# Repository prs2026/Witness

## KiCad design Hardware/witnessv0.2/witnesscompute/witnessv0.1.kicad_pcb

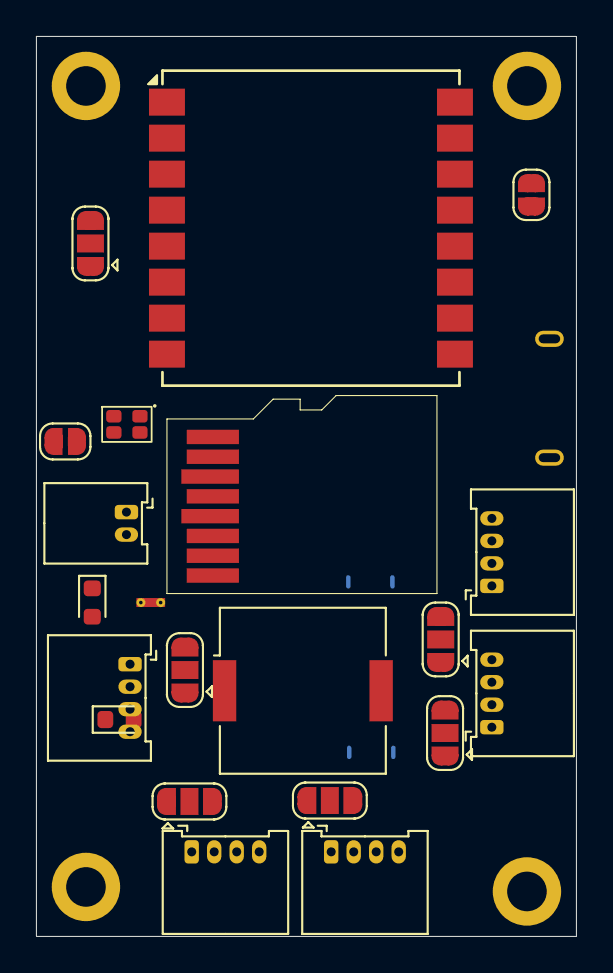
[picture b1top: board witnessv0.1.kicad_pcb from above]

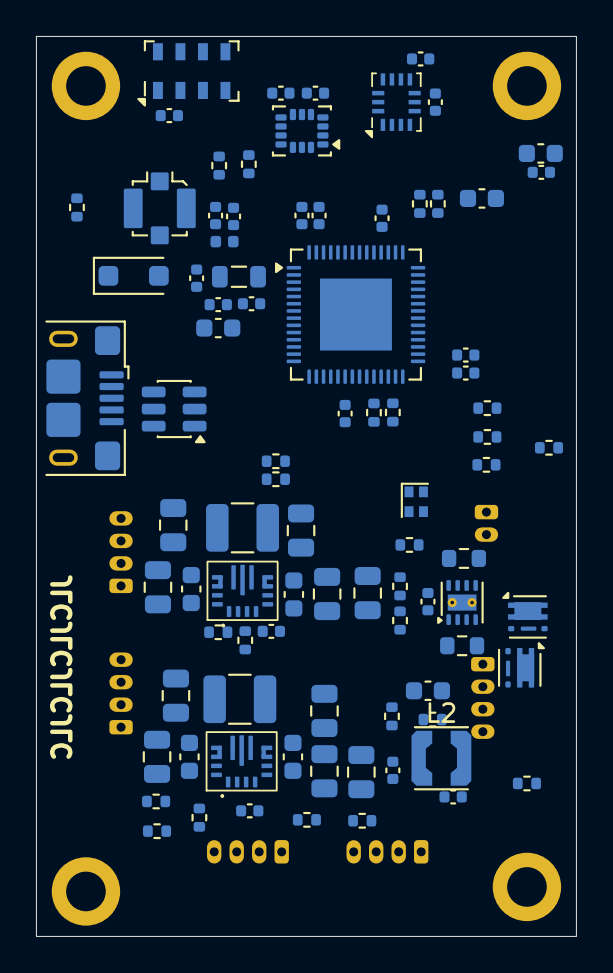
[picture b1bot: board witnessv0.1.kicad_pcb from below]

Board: 4 copper layers, 30.0 x 50.0 mm, 111 parts (87 on the bottom side), 57 nets, no tracks yet.

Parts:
AE1: Antenna_Shield; U.FL_Molex_MCRF_73412-0110_Vertical
BZ1: Buzzer; Buzzer_Murata_PKMCS0909E
C3, C4, C5, C7, C15, C16, C21, C26, C27, C28, C29, C32, C33, C34, C36, C37, C38, C39, C40, C42: 100n; C_0402_1005Metric
C6, C30: 1u; C_0402_1005Metric
C8, C9, C20, C22, C31, C41, C43: 10u; C_0603_1608Metric
C10, C11, C18, C19: 10u; C_0805_2012Metric
C12, C13, C14, C23, C24, C25: 22u; C_0805_2012Metric
C17: 470n; C_0603_1608Metric
D1: LED_RGBA; 0603x2 RGB
D2, D3: LED; LED_0603_1608Metric
D4: PMEG2020EH,115; D_SOD-123F
H4, H5, H6, H7: MountingHole_Pad; MountingHole_2.2mm_M2_DIN965_Pad
J1, J4: Conn_01x02; SolderJumper-2_P1.3mm_Open_RoundedPad1.0x1.5mm
J2: Conn_01x02; Molex_Micro_Lock_2200980271_01x02_Horizontal
J3: USB_B_Micro; USB_Micro-B_Amphenol_10118193-0002LF_Horizontal
J5, J6, J7, J8, J9: Conn_01x04; Molex_MicroLock-2200980471-01x04-Horizontal
J10: Micro_SD_Card; microSD_Card
JP1, JP2, JP3, JP4, JP5, JP6: SolderJumper_3_Open; SolderJumper-3_P1.3mm_Open_RoundedPad1.0x1.5mm
L1, L3: 1u; L_1210_3225Metric
L2: 2.2u; L_Coilcraft_LPS3010
L4: 10n; L_0805_2012Metric
L5: L_Small; L_0402_1005Metric
Q1, Q2: SQA403EJ; Vishay_PowerPAK_SC70-6L_Single
R1, R9: 100k; R_0402_1005Metric
R2: 470k; R_0402_1005Metric
R3: 150k; R_0402_1005Metric
R5: 4.7; R_0402_1005Metric
R6, R10, R12: 10k; R_0402_1005Metric
R7: 680k; R_0402_1005Metric
R8: 130k; R_0402_1005Metric
R11: 35k; R_0402_1005Metric
R17, R18, R19, R20, R21, R22: 1k; R_0402_1005Metric
R23, R24, R25, R26, R27, R28, R29: 4.7k; R_0402_1005Metric
R30, R31: 0; R_0402_1005Metric
R33, R34: 2.5m; R_0603_1608Metric
U1: ESP32-S3FN8; QFN-56-1EP_7x7mm_P0.4mm_EP4x4mm
U2, U6: TPS63070; RNM0015A
U3: INA2180A3IDSG; Texas_DSG0008A_WSON-8-1EP_2x2mm_P0.5mm_EP0.9x1.6mm_ThermalV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
U4: LSM6DSV320XTR; Bosch_LGA-14_3x2.5mm_P0.5mm
U5: ICM-45686; LGA-14_3x2.5mm_P0.5mm_LayoutBorder3x4y
U7: MS5607-02BA; LGA-8_3x5mm_P1.25mm
U9: USBLC6-2SC6; SOT-23-6
U10: RA-01SH-P; Ai-Thinker-Ra-01-LoRa
Y1: F322540MUBCE2O; Oscillator_SMD_Abracon_ASCO-4Pin_1.6x1.2mm

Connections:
+3V3: C3.1, C4.1, C5.1, C6.1, C16.1, C26.1, C27.1, C29.1, C30.1, C31.1, C34.1, C36.1, C37.1, C38.1, C39.1, C40.1, C41.1, C42.1, D1.4 (A), D2.2 (A), JP1.3 (B), JP2.3 (B), JP3.3 (B), JP4.3 (B), JP5.3 (B), JP6.1 (A), L2.2, L4.1, R5.1, R22.2, R23.2, R25.2, R26.2, R28.2, U1.20 (VDD3P3_RTC), U1.29 (VDD_SPI), U1.46 (VDD3P3_CPU), U1.55 (VDDA), U1.56 (VDDA), U3.8 (VS), U4.5 (VDDIO), U4.8 (VDD), U5.5 (VDDIO), U5.8 (VDD), U7.1 (VDD), U10.3 (VDD), Y1.1 (Tri-State), Y1.4 (VDD)
+5V: D3.2 (A), JP1.1 (A), JP2.1 (A), JP3.1 (A), JP4.1 (A), JP5.1 (A), JP6.3 (B), R34.2, U3.6 (-)
+BATT: J2.1, Q2.1 (D)
/IO/RXD_MCU: J5.3, J7.3, J8.3, J9.3
/IO/TXD_MCU: J5.2, J7.2, J8.2, J9.2
/IO/USB_D+: U9.1 (I/O1), U9.3 (I/O2)
/MCU/GPIO0: J4.1, R23.1, U1.5 (GPIO0)
/MCU/GPIO3: R28.1, R29.2, U1.8 (GPIO3)
/MCU/GPIO45: R26.1, R27.2, U1.51 (GPIO45)
/MCU/GPIO46: R24.2, R25.1, U1.52 (GPIO46)
/MCU/RST: J1.1, R22.1, U1.4 (CHIP_PU)
/MCU/XIN: U1.54 (XTAL_P), Y1.3 (OUT)
/Power/5VSENSE+: C22.1, C23.1, C24.1, C25.1, R7.1, R9.1, R34.1, U3.5 (+), U6.7 (VOUT), U6.8 (VOUT)
/Power/BATT_POSTSW: C9.1, C10.1, C11.1, C18.1, C19.1, C20.1, R6.1, R11.1, R12.1, R33.2, U2.12 (VIN), U2.13 (VIN), U3.2 (-), U6.12 (VIN), U6.13 (VIN)
/Power/ISENSE+: Q1.4 (S), R33.1, U3.3 (+)
/Sensors/I2C_SCL: U4.13 (SCL), U5.3 (MAS_CLK)
/Sensors/I2C_SDA: U4.14 (SDA), U5.2 (MAS_DA)
/Sensors/MS56_CS: U7.4 (CSB), U7.5 (CSB)
/Sensors/SPI1_CIPO: U4.1 (SDO/SA0), U5.1 (AP_SDO), U7.6 (SDO)
/Sensors/SPI1_COPI: U4.3 (SCX), U5.14 (AP_SDIO), U7.7 (SDI/SDA)
/Sensors/SPI1_SCLK: U4.2 (SDX), U5.11 (AP_SCLK), U7.8 (SCLK)
GND: AE1.2 (Shield), BZ1.2 (-), C3.2, C4.2, C5.2, C6.2, C7.2, C8.2, C9.2, C10.2, C11.2, C12.2, C13.2, C14.2, C15.2, C16.2, C17.2, C18.2, C19.2, C20.2, C21.2, C22.2, C23.2, C24.2, C25.2, C26.2, C27.2, C28.2, C29.2, C30.2, C31.2, C32.2, C33.2, C34.2, C36.2, C37.2, C38.2, C39.2, C40.2, C41.2, C42.2, C43.1, H4.1 (1_1), H5.1 (1_1), H6.1 (1_1), H7.1 (1_1), J1.2, J2.2, J3.5 (GND), J4.2, J5.4, J6.4, J7.4, J8.4, J9.4, Q1.3 (G), R3.2, R8.2, R10.2, R20.1, R21.1, R24.1, R27.1, R29.1, U1.57 (GND), U2.4 (GND), U2.6 (FB2), U2.10 (PGND), U2.15 (VSEL), U3.4 (GND), U3.9 (EP), U4.6 (GND), U4.7 (GND), U5.6 (GND), U6.4 (GND), U6.6 (FB2), U6.10 (PGND), U6.15 (VSEL), U7.2 (PS), U7.3 (GND), U9.2 (GND), U10.2 (GND), U10.9 (GND), U10.16 (GND), Y1.2 (GND)
unnamed: AE1.1 (A), C33.1, L5.2
unnamed: C8.1, C12.1, C13.1, C14.1, C15.1, L2.1, R1.1, R2.1, U2.7 (VOUT), U2.8 (VOUT)
unnamed: C17.1, R5.2
unnamed: C28.1, L4.2, U1.2 (VDD3P3), U1.3 (VDD3P3)
unnamed: D1.3 (BK), R19.2
unnamed: D1.2 (GK), R17.2
unnamed: D1.1 (RK), R18.2
unnamed: D2.1 (K), R20.2
unnamed: D3.1 (K), R21.2
unnamed: D4.1 (K), Q1.1 (D), Q2.4 (S)
unnamed: J3.3 (D+), U9.6 (I/O1)
unnamed: J3.2 (D-), U9.4 (I/O2)
unnamed: J5.1, JP1.2 (C)
unnamed: J6.1, JP2.2 (C)
unnamed: J7.1, JP3.2 (C)
unnamed: J8.1, JP4.2 (C)
unnamed: J9.1, JP5.2 (C)
unnamed: C43.2, JP6.2 (C), U10.5 (VCC_PA)
unnamed: R30.2, U1.25 (GPIO19/USB_D-)
unnamed: R31.2, U1.26 (GPIO20/USB_D+)
unnamed: C32.1, L5.1, U1.1 (LNA_IN)
unnamed: R10.1, R11.2, U2.14 (EN)
unnamed: R2.2, R3.1, U2.5 (FB)
unnamed: L1.1, U2.11 (L1)
unnamed: L1.2, U2.9 (L2)
unnamed: R1.2, U2.2 (PG)
unnamed: R12.2, U2.1 (PS/SYNC)
unnamed: C7.1, U2.3 (VAUX)
unnamed: R7.2, R8.1, U6.5 (FB)
unnamed: L3.1, U6.11 (L1)
unnamed: L3.2, U6.9 (L2)
unnamed: R9.2, U6.2 (PG)
unnamed: R6.2, U6.1 (PS/SYNC)
unnamed: C21.1, U6.3 (VAUX)
VBUS: D4.2 (A), J3.1 (VBUS), Q2.3 (G), U9.5 (VBUS)
